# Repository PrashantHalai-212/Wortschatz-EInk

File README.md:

# Wortschatz – E-Ink German Vocabulary Device

Battery-powered e-ink device that shows random German words with their grammar. Built around an ESP32-S3, designed in KiCad 10, 4-layer PCB made by JLCPCB, hand-assembled.

## Specs

| | |
|---|---|
| **MCU** | ESP32-S3-WROOM-1-N16R8 (16 MB flash, 8 MB PSRAM, Wi-Fi/BLE, native USB) |
| **Display** | WeAct 2.9" e-paper, 296 × 128, SSD1680, SPI |
| **Storage** | microSD (Molex 104031-0811), SPI, card detect |
| **Battery** | 820 mAh Li-Po, JST PH, built-in protection |
| **Charging** | TI BQ25170 linear charger, 400 mA, 4.2 V |
| **Fuel gauge** | Maxim MAX17055 (ModelGauge m5), 10 mΩ sense resistor |
| **Power path** | TI TPS2116 power mux (USB priority) → RT9080 3.3 V LDO |
| **SD power** | TI TPS22929D load switch |
| **USB** | USB-C (5.1 kΩ CC pull-downs), USBLC6-2 ESD protection |
| **Inputs** | 4 side buttons (wake from deep sleep), EN and BOOT buttons |
| **PCB** | 4 layers, 92.0 × 38.5 mm, 1.6 mm, mostly 0402 parts |

## Design decisions

**Power path (TPS2116):** switches between USB and battery automatically, with no diode voltage drop. A 220k/100k divider on PR1 gives USB priority, and the battery takes over the moment USB is unplugged.

**Charging (BQ25170):** a simple linear Li-ion charger set by three resistors.
- `ISET = 750 Ω` → 300 / 750 = **400 mA**, about 0.5C for the 820 mAh cell, so a full charge takes about 2–2.5 h
- `VSET = 27 kΩ` → **4.2 V** charge voltage
- The `STAT` output goes to a GPIO to show a charging indicator

**Battery percentage (MAX17055):** a real fuel gauge instead of guessing from battery voltage. It measures current through a 10 mΩ resistor in the battery's negative lead and reports over I²C, with an alert pin for low battery.

**Low power:**
- The ESP32 sleeps between button presses. All 4 buttons are on RTC GPIOs, so any press wakes it (ext1 wake-up).
- The e-paper keeps its image without power.
- The SD card's supply is fully switched off by a TPS22929 load switch, with a pull-down so it stays off during sleep. The SD pull-ups sit on the switched rail, so nothing leaks into the unpowered card.

**PCB:** 4-layer stackup with signals / solid GND / split power planes / signals. The ESP32 antenna overhangs the board edge with a copper keep-out, there are GND stitching vias, thermal vias under the charger's exposed pad, and test points on every power rail, I²C and UART0.

## Pin map

| Function | GPIO |
|---|---|
| Buttons 1–4 | IO4, IO6, IO7, IO1 |
| SPI MOSI / SCK (shared) | IO11 / IO12 |
| E-paper CS / DC / RST / BUSY | IO10 / IO8 / IO9 / IO14 |
| SD CS / MISO | IO15 / IO13 |
| SD power enable / card detect | IO21 / IO5 (0 = card inserted) |
| Fuel gauge SDA / SCL / ALERT | IO41 / IO42 / IO40 |
| Charger status | IO38 |
| USB D− / D+ | IO19 / IO20 |
| UART0 TX / RX (test pads) | IO43 / IO44 |
| BOOT | IO0 |

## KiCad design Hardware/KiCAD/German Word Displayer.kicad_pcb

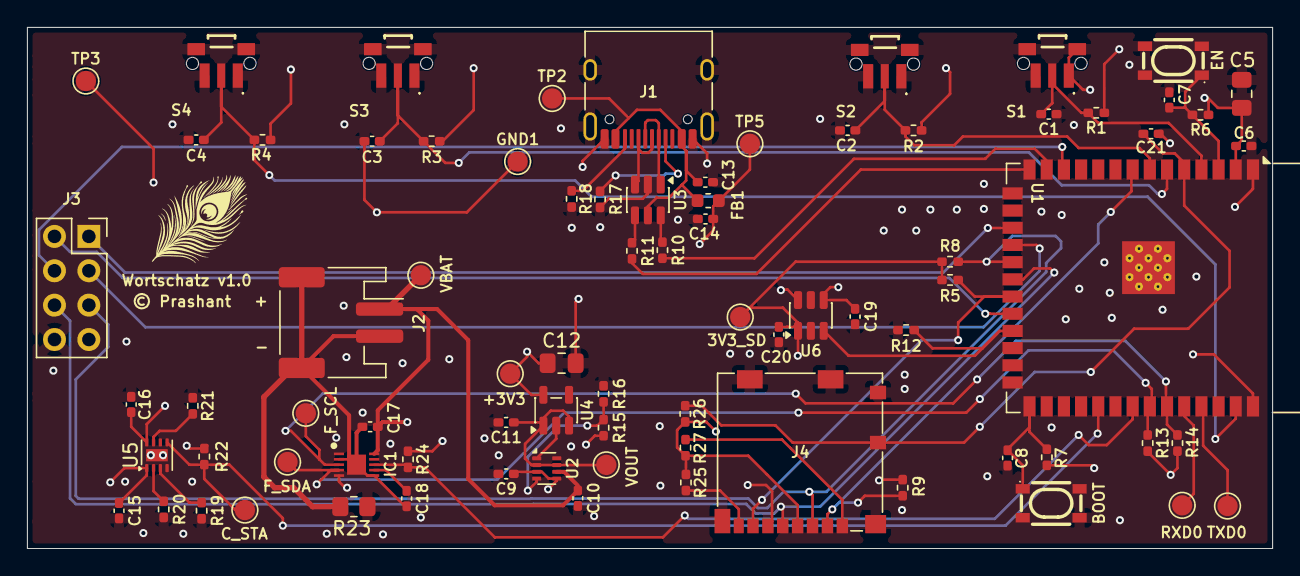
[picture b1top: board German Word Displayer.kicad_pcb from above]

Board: 4 copper layers, 92.0 x 38.5 mm, 79 parts (0 on the bottom side), 45 nets.

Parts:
3V3_SD: 3V3_SD; TestPoint_Pad_D1.5mm
+3V3: 3V3; TestPoint_Pad_D1.5mm
BOOT: SKRPABE010
C1, C2, C3, C4, C13, C14, C17, C21: 100nF; C_0402_1005Metric_Pad0.74x0.62mm_HandSolder
C5: 22u/10V; C_0805_2012Metric_Pad1.18x1.45mm_HandSolder
C6, C8: 0.1uF; C_0402_1005Metric_Pad0.74x0.62mm_HandSolder
C7, C20: 1uF; C_0402_1005Metric_Pad0.74x0.62mm_HandSolder
C9, C10, C11, C15, C16, C19: 1u/25V; C_0402_1005Metric_Pad0.74x0.62mm_HandSolder
C12: 10u/25V; C_0805_2012Metric_Pad1.18x1.45mm_HandSolder
C18: 0.47uF; C_0402_1005Metric_Pad0.74x0.62mm_HandSolder
C_STA: C_STAT; TestPoint_Pad_D1.5mm
EN: SKRPABE010
FB1: 600R@100MHz; L_0603_1608Metric
F_SCL: F_SCL; TestPoint_Pad_D1.5mm
F_SDA: F_SDA; TestPoint_Pad_D1.5mm
GND1: GND; TestPoint_Pad_D1.5mm
IC1: MAX17055ETB+T
J1: USB_C_Receptacle_USB2.0_16P; USB_C_Receptacle_HRO_TYPE-C-31-M-12
J2: S2B-PH-SM4-TB(LF)(SN); JST_PH_S2B-PH-SM4-TB_1x02-1MP_P2.00mm_Horizontal
J3: E-INK DISPLAY; PinSocket_2x04_P2.54mm_Vertical
J4: Micro_SD_Card_Det2; microSD_HC_Molex_104031-0811
R1, R2, R3, R4, R5, R6, R7, R8, R9, R19, R22, R24, R25, R26, R27: 10k; R_0402_1005Metric_Pad0.72x0.64mm_HandSolder
R10, R11: 22R; R_0402_1005Metric_Pad0.72x0.64mm_HandSolder
R12, R16: 100k; R_0402_1005Metric_Pad0.72x0.64mm_HandSolder
R13, R14: 4.7k; R_0402_1005Metric_Pad0.72x0.64mm_HandSolder
R15: 220k; R_0402_1005Metric_Pad0.72x0.64mm_HandSolder
R17, R18: 5k1; R_0402_1005Metric_Pad0.72x0.64mm_HandSolder
R20: 750; R_0402_1005Metric_Pad0.72x0.64mm_HandSolder
R21: 27k; R_0402_1005Metric_Pad0.72x0.64mm_HandSolder
R23: 10m; R_0805_2012Metric_Pad1.20x1.40mm_HandSolder
RXD0: RXD0; TestPoint_Pad_D1.5mm
S1, S2, S3, S4: SKRTLAE010
TP2: VBUS; TestPoint_Pad_D1.5mm
TP3: GND; TestPoint_Pad_D1.5mm
TP5: VBUS_FILT; TestPoint_Pad_D1.5mm
TXD0: TXD0; TestPoint_Pad_D1.5mm
U1: ESP32-S3-WROOM-1
U2: TPS2116DRL; SOT-583-8
U3: USBLC6-2SC6; SOT-23-6
U4: RT9080-33GJ5; TSOT-23-5
U5: BQ25170DSGR; Texas_DSG0008A_WSON-8-1EP_2x2mm_P0.5mm_EP0.9x1.6mm
U6: TPS22929D; SOT-23-6
VBAT: VBAT; TestPoint_Pad_D1.5mm
VOUT: VOUT; TestPoint_Pad_D1.5mm

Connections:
+3V3: +3V3.1 (1_1), C5.1, C6.1, C12.1, C19.1, J3.7, R1.1, R2.1, R3.1, R4.1, R6.1, R7.1, R13.1, R14.1, R22.2, R24.2, U1.2 (3V3), U4.5 (OUT), U6.4 (VIN), U6.6 (VIN)
+3V3_SD: 3V3_SD.1 (1_1), C20.1, J4.4 (VDD), R5.2, R8.1, R9.2, R25.2, R26.1, R27.2, U6.1 (VOUT)
/CHARGER & FUEL/FUEL_REG: C18.1, IC1.7 (REG)
/ESP32-S3/USBCN: R10.2, U1.13 (USB_D-)
/ESP32-S3/USBCP: R11.2, U1.14 (USB_D+)
/POWER/USBC_N: J1.A7 (D-), J1.B7 (D-), U3.1 (I/O1)
/POWER/USBC_P: J1.A6 (D+), J1.B6 (D+), U3.3 (I/O2)
/SD_Card/DAT1: J4.8 (DAT1), R25.1
/SD_Card/DAT2: J4.1 (DAT2), R27.1
BATT_GND: C17.2, C18.2, IC1.2 (AIN), IC1.6 (CSP_1), IC1.11 (CSP_2), J2.2, J2.MP (MountPin), R23.1
BOOT: BOOT.1, C8.1, R7.2, U1.27 (IO0)
BTN1: C1.1, R1.2, S1.2, U1.4 (IO4)
BTN2: C3.1, R3.2, S3.2, U1.6 (IO6)
BTN3: C2.1, R2.2, S2.2, U1.7 (IO7)
BTN4: C4.1, R4.2, S4.2, U1.39 (IO1)
BUSY: J3.2, U1.22 (IO14)
C_STAT: C_STA.1 (1_1), R22.1, U1.31 (IO38), U5.5 (STAT)
D_CS: J3.3, U1.18 (IO10)
D/C: J3.4, U1.12 (IO8)
EN: C7.1, EN.1, R6.2, U1.3 (EN)
FUEL_ALERT: IC1.8 (ALRT), R24.1, U1.33 (IO40)
FUEL_SCL: F_SCL.1 (1_1), IC1.3 (SCL), R14.2, U1.35 (IO42)
FUEL_SDA: F_SDA.1 (1_1), IC1.4 (SDA), R13.2, U1.34 (IO41)
GND: BOOT.4, C1.2, C2.2, C3.2, C4.2, C5.2, C6.2, C7.2, C8.2, C9.2, C10.2, C11.2, C12.2, C13.2, C14.2, C15.2, C16.2, C19.2, C20.2, C21.2, EN.4, GND1.1 (1_1), IC1.5 (CSN), J1.A1 (GND), J1.A12 (GND), J1.B1 (GND), J1.B12 (GND), J1.SH (SHIELD), J3.8, J4.6 (VSS), J4.10 (DET_A), J4.SH (SHIELD), R12.2, R16.1, R17.2, R18.2, R19.2, R20.2, R21.2, R23.2, S1.1, S1.3, S1.MP1, S1.MP2, S2.1, S2.3, S2.MP1, S2.MP2, S3.1, S3.3, S3.MP1, S3.MP2, S4.1, S4.3, S4.MP1, S4.MP2, TP3.1 (1_1), U1.1 (GND), U1.40 (GND), U1.41 (GND), U2.1 (GND), U3.2 (GND), U4.2 (GND), U5.4 (GND), U5.9 (PAD), U6.2 (GND), U6.5 (GND)
MOSI: J3.5, J4.3 (CMD), R8.2, U1.19 (IO11)
unnamed: J1.A5 (CC1), R17.1
unnamed: J1.B5 (CC2), R18.1
unnamed: RXD0.1 (1_1), U1.36 (RXD0)
unnamed: TXD0.1 (1_1), U1.37 (TXD0)
unnamed: R15.1, R16.2, U2.4 (PR1)
unnamed: R20.1, U5.2 (ISET)
unnamed: R19.1, U5.3 (TS)
unnamed: R21.1, U5.7 (VSET)
RES: J3.1, U1.17 (IO9)
SCK: J3.6, J4.5 (CLK), U1.20 (IO12)
SD_CS: J4.2 (DAT3/CD), R9.1, U1.8 (IO15)
SD_DET: C21.1, J4.9 (DET_B), R26.2, U1.5 (IO5)
SD_MISO: J4.7 (DAT0), R5.1, U1.21 (IO13)
SD_ON: R12.1, U1.23 (IO21), U6.3 (ON)
USB_N: R10.1, U3.6 (I/O1)
USB_P: R11.1, U3.4 (I/O2)
VBAT: C10.1, C16.1, C17.1, IC1.10 (BATT), J2.1, U2.6 (VIN2), U5.8 (OUT), VBAT.1 (1_1)
VBUS: C13.1, FB1.1, J1.A4 (VBUS), J1.A9 (VBUS), J1.B4 (VBUS), J1.B9 (VBUS), TP2.1 (1_1), U3.5 (VBUS)
VBUS_filtered: C9.1, C14.1, C15.1, FB1.2, R15.2, TP5.1 (1_1), U2.3 (VIN1), U2.5 (MODE), U5.1 (IN)
VOUT: C11.1, U2.2 (VOUT), U2.7 (VOUT), U4.1 (IN), U4.3 (EN), VOUT.1 (1_1)

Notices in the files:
Hardware/KiCAD/German Word Displayer.kicad_pcb:
© Prashant
